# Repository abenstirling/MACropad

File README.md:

# MACropad
#### Open-Source Macropad, in form factor of the iconic Apple Computer Macintosh. 

### Functionality
---
- 6 Customizable Keys
- 2 Rotary Encoders
- RGB-powered Lights
- eInk Display

### Hardware
---
- Custom PCB, powered by the RPI Pico
- 3D Printed Case
- Headphone Jack UART Communication between MAC and Pad

### Software
---
- Embedded Rust

### Repo Structured as follows: 
```
MACropad
├── Firmware
│   ├── Cargo.toml
│   ├── Cargo.lock
│   ├── src
│   │   ├── main.rs
│   │   ├── lib.rs
│   │   ├── rotary.rs
│   │   ├── key.rs
│   │   ├── display.rs
│   │   ├── led.rs
│   │   ├── uart.rs
│   │   ├── usb.rs
│   │   ├── usb_desc.rs
│   │   ├── usb_strings.rs
├── ECAD
│   ├── MACropad.gerber
│   ├── MACropad.bom
├── MCAD
│   ├── case.step
│   ├── case.stl
│   ├── case.gcode
├── Images
│   ├── MACropad.png
├── LICENSE
├── README.md
├── .gitignore

```

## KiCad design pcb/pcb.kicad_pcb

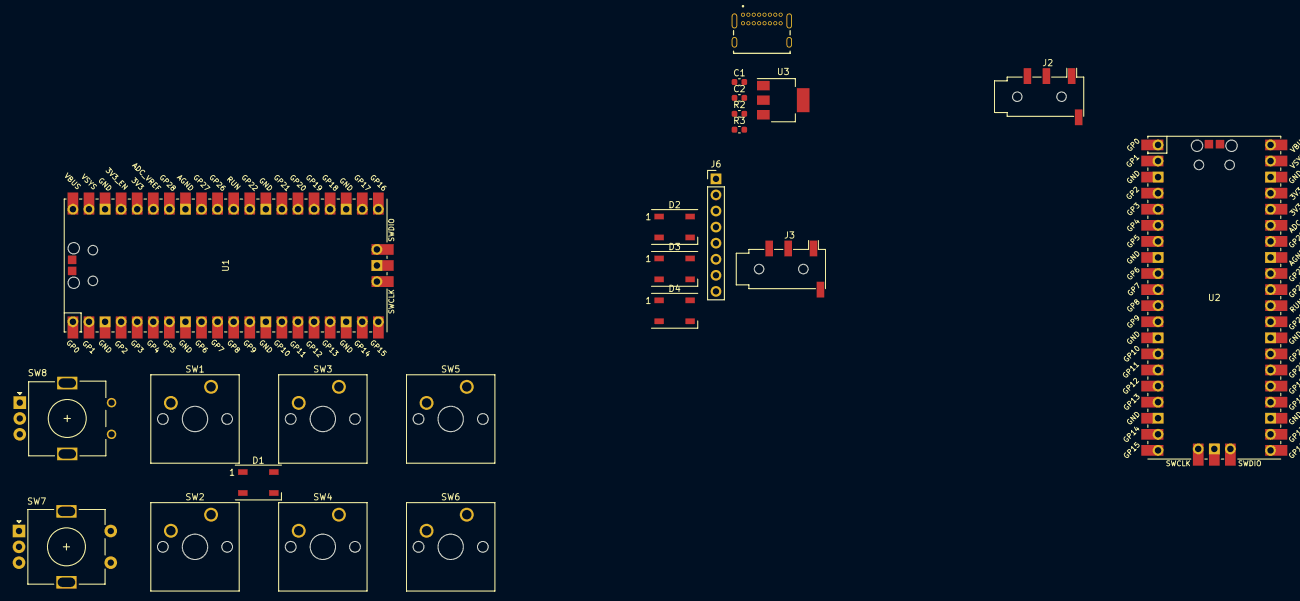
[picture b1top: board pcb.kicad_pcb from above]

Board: 2 copper layers, 23 parts (0 on the bottom side), 35 nets, no tracks yet.

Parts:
C1, C2: 10u; C_0603_1608Metric
D1, D2, D3, D4: SK6812MINI; LED_WS2812B_PLCC4_5.0x5.0mm_P3.2mm
J1: USB4085-GF-A_REVB; GCT_USB4085-GF-A_REVB
J2, J3: AudioJack4; Jack_3.5mm_PJ320D_Horizontal
J6: Conn_01x08_Pin; PinHeader_1x08_P2.54mm_Vertical
R2, R3: 5k1; C_0603_1608Metric
SW1, SW2, SW3, SW4, SW5, SW6: SW_Push; SW_Cherry_MX_1.00u_PCB
SW7: RotaryEncoder_Switch; RotaryEncoder_Alps_EC11E-Switch_Vertical_H20mm
SW8: RotaryEncoder_Switch; RotaryEncoder_Alps_EC11E_Vertical_H20mm
U1, U2: Pico; RPi_Pico_SMD_TH
U3: LM1117MP-5.0; SOT-223-3_TabPin2

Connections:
/3.3v: J6.8, U2.36 (3V3)
/BUSY: J6.1, U2.10 (GPIO7)
/Button_1: SW1.1, U1.2 (GPIO1)
/Button_2: SW2.1, U1.4 (GPIO2)
/Button_3: SW3.1, U1.5 (GPIO3)
/Button_4: SW4.1, U1.6 (GPIO4)
/Button_5: SW5.1, U1.7 (GPIO5)
/Button_6: SW6.1, U1.9 (GPIO6)
/Button_7: SW7.S1, U1.10 (GPIO7)
/CLK: J6.5, U2.4 (GPIO2)
/CS: J6.4, U2.2 (GPIO1)
/D+: J1.A6 (DP1), J1.B6 (DP2)
/D-: J1.A7 (DN1), J1.B7 (DN2)
/DC: J6.3, U2.9 (GPIO6)
/DIN: J6.6, U2.5 (GPIO3)
/LED_SIGNAL: D1.3 (DIN), U1.20 (GPIO15)
/RST: J6.2, U2.6 (GPIO4)
/RX_MAC: J3.T, U2.21 (GPIO16)
/RX_PAD: J2.R1, U1.21 (GPIO16)
/Rotary_1A: SW7.A, U1.14 (GPIO10)
/Rotary_1B: SW7.B, U1.15 (GPIO11)
/Rotary_2A: SW8.A, U1.16 (GPIO12)
/Rotary_2B: SW8.B, U1.17 (GPIO13)
/TX_MAC: J3.R1, U2.22 (GPIO17)
/TX_PAD: J2.T, U1.22 (GPIO17)
/VBUS_PAD: C1.1, J2.S, U3.3 (VI)
/VIN_MAC: J1.A4 (VBUS), J1.A9 (VBUS), J1.B4 (VBUS), J1.B9 (VBUS), J3.S, U2.40 (VBUS)
/VREG_PAD: C2.1, D1.4 (VDD), D2.4 (VDD), D3.4 (VDD), D4.4 (VDD), U1.40 (VBUS), U3.2 (VO)
GND: C1.2, C2.2, D1.2 (VSS), D2.2 (VSS), D3.2 (VSS), D4.2 (VSS), J1.A1 (GND), J1.A12 (GND), J1.B1 (GND), J1.B12 (GND), J2.R2, J3.R2, J6.7, R2.1, R3.1, SW1.2, SW2.2, SW3.2, SW4.2, SW5.2, SW6.2, SW7.C, SW7.S2, SW8.C, U1.3 (GND), U1.8 (GND), U1.13 (GND), U1.18 (GND), U1.23 (GND), U1.28 (GND), U1.38 (GND), U2.3 (GND), U2.8 (GND), U2.13 (GND), U2.18 (GND), U2.23 (GND), U2.28 (GND), U2.38 (GND), U3.1 (GND)
unnamed: D1.1 (DOUT), D2.3 (DIN)
unnamed: D2.1 (DOUT), D3.3 (DIN)
unnamed: D3.1 (DOUT), D4.3 (DIN)
unnamed: J1.A5 (CC1), R2.2
unnamed: J1.B5 (CC2), R3.2
unnamed: J1.S1 (SHELL), J1.S2 (SHELL), J1.S3 (SHELL), J1.S4 (SHELL)

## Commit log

2023-09-15 added rp-display-test
2023-09-20 More KiCAD
2023-09-21 Changes on MACmini
2023-09-21 Adding footprint/symbol
2023-09-22 Schematic Donezo
2023-10-10 ECAD, MCAD completed
